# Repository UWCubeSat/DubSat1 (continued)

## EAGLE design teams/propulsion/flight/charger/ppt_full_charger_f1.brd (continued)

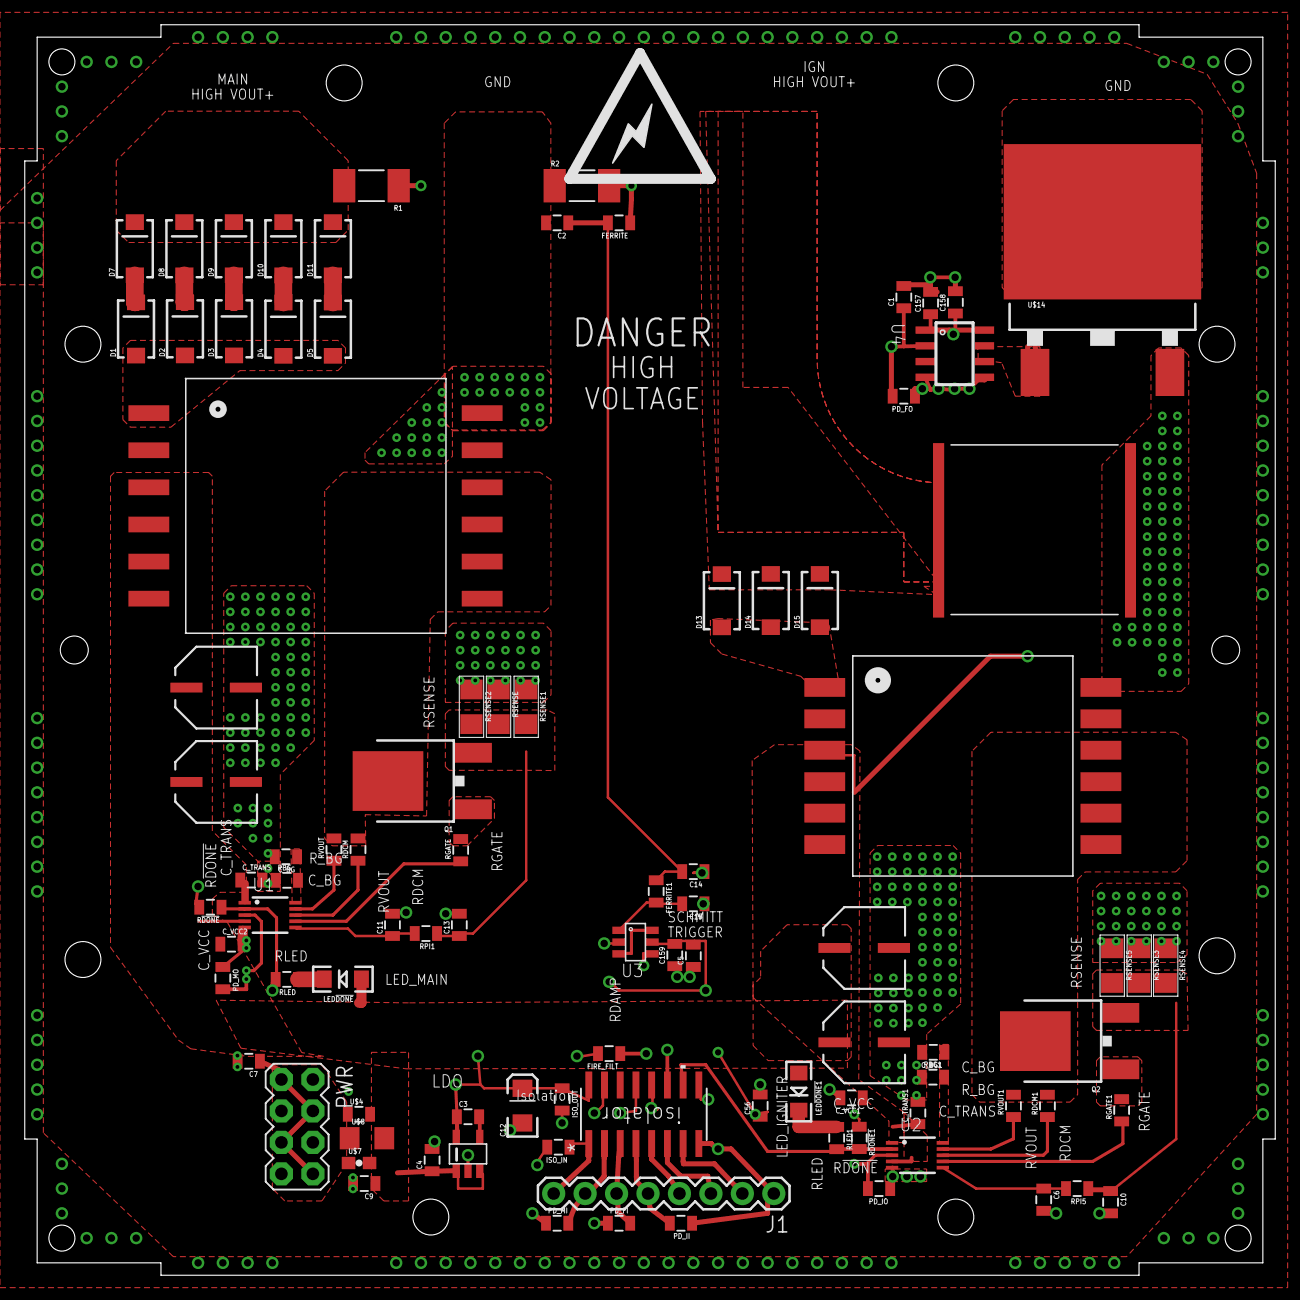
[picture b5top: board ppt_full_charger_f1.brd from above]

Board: 4 copper layers, 101.0 x 101.0 mm, 94 parts (0 on the bottom side), 51 nets.

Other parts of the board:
U$3: ICON_BOLT-L

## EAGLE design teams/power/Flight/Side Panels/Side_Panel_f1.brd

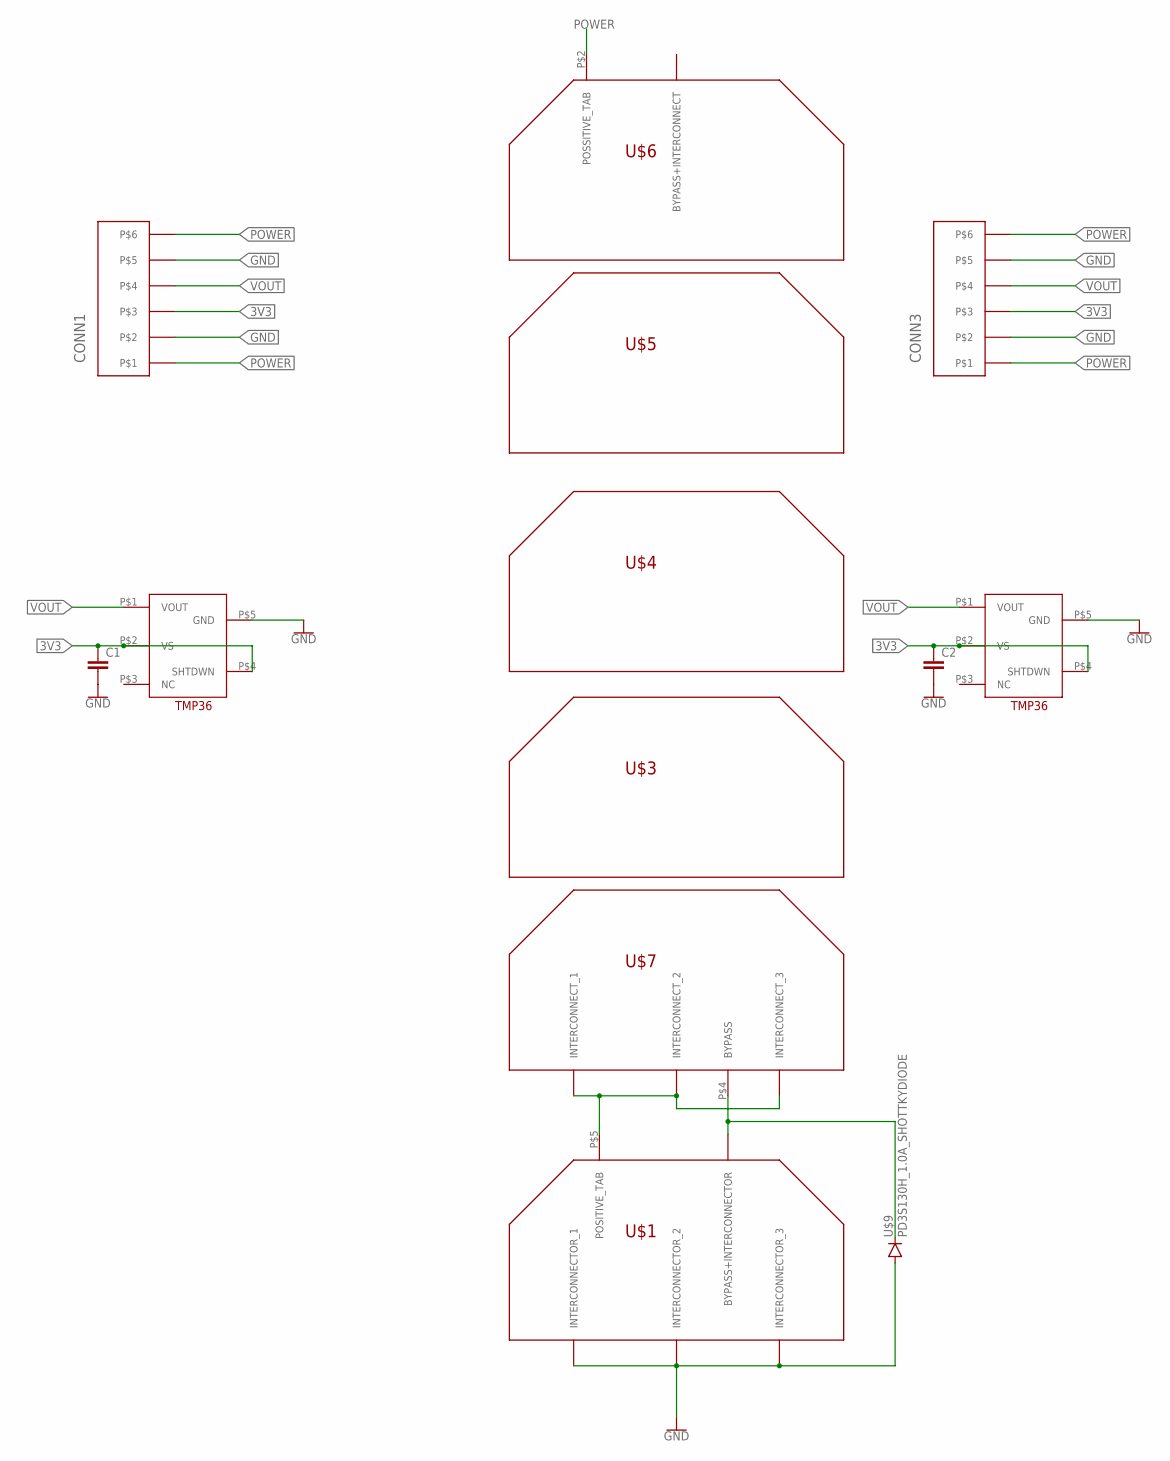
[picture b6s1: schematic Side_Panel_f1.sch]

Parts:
C1, C2: CAPACITOR0805; 0805
CONN1, CONN3: PICOLOCK_6PICOLOCK_6; PICOLOCK_6
U$1: SOLAR_CELL_STAND-ALONE
U$2, U$8: TMP36; SOT-23-5
U$3, U$4, U$5: SOALAR_CELL_OUTLINE; SOLAR_CELL_OUTLINE
U$6: SOLAR_CELL_TOP; SOLAR_CELL_TOP_SHORT-PAD
U$7: SOLAR_CELL_BOTTOM+BYPASS
U$9: PD3S130H_1.0A_SHOTTKYDIODE; POWERDI_323

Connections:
3V3: C1.1, C2.1, CONN1.P$3, CONN3.P$3, U$2.P$2 (VS), U$2.P$4 (SHTDWN), U$8.P$2 (VS), U$8.P$4 (SHTDWN)
GND: C1.2, C2.2, CONN1.P$2, CONN1.P$5, CONN3.P$2, CONN3.P$5, U$1.P$1 (INTERCONNECTOR_1), U$1.P$2 (INTERCONNECTOR_2), U$1.P$3 (INTERCONNECTOR_3), U$2.P$5 (GND), U$8.P$5 (GND), U$9.P$2 (A)
unnamed: U$1.P$4 (BYPASS+INTERCONNECTOR), U$7.P$4 (BYPASS), U$9.P$1 (C)
unnamed: U$1.P$5 (POSITIVE_TAB), U$7.P$1 (INTERCONNECT_1), U$7.P$2 (INTERCONNECT_2), U$7.P$3 (INTERCONNECT_3)
POWER: CONN1.P$1, CONN1.P$6, CONN3.P$1, CONN3.P$6, U$6.P$2 (POSSITIVE_TAB)
VOUT: CONN1.P$4, CONN3.P$4, U$2.P$1 (VOUT), U$8.P$1 (VOUT)

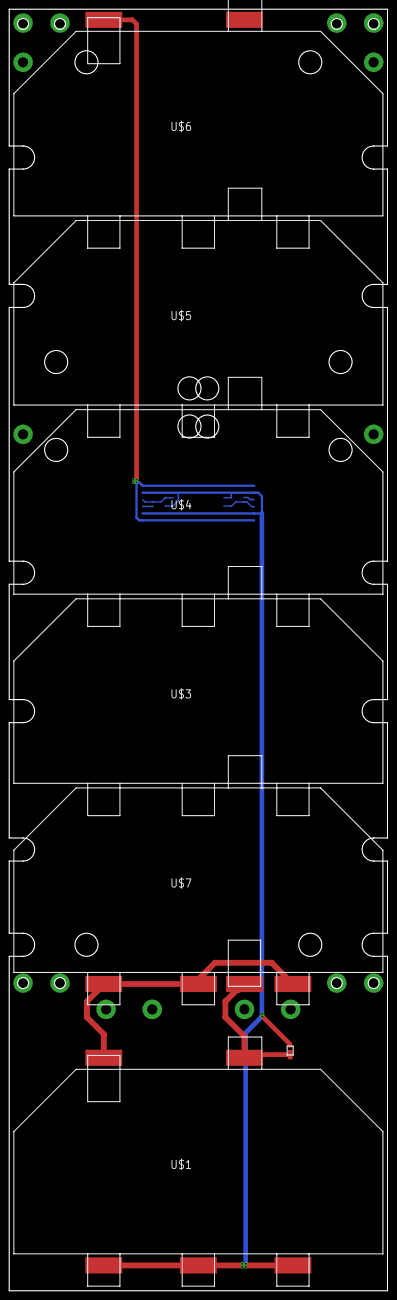
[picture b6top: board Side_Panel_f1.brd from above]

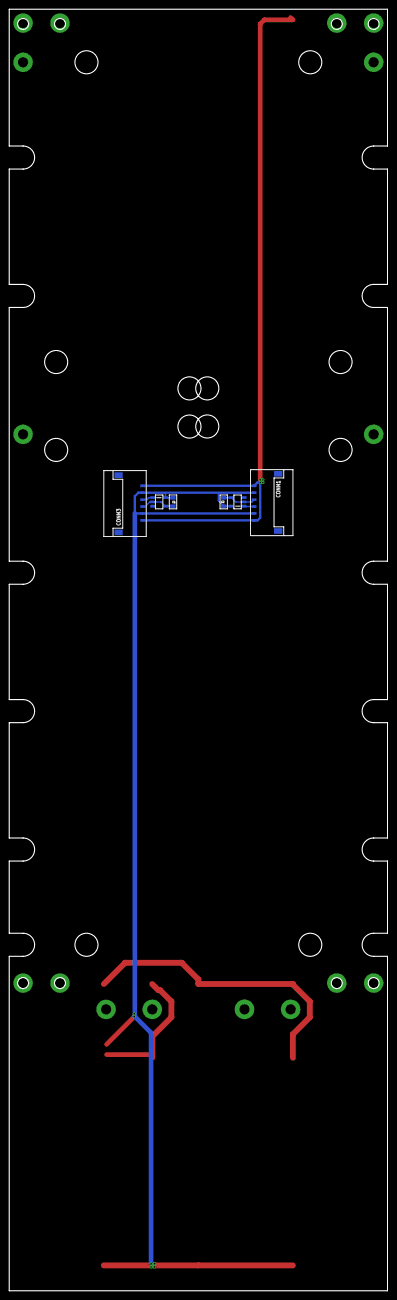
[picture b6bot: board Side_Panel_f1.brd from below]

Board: 2 copper layers, 82.0 x 277.8 mm, 13 parts (6 on the bottom side), 6 nets.

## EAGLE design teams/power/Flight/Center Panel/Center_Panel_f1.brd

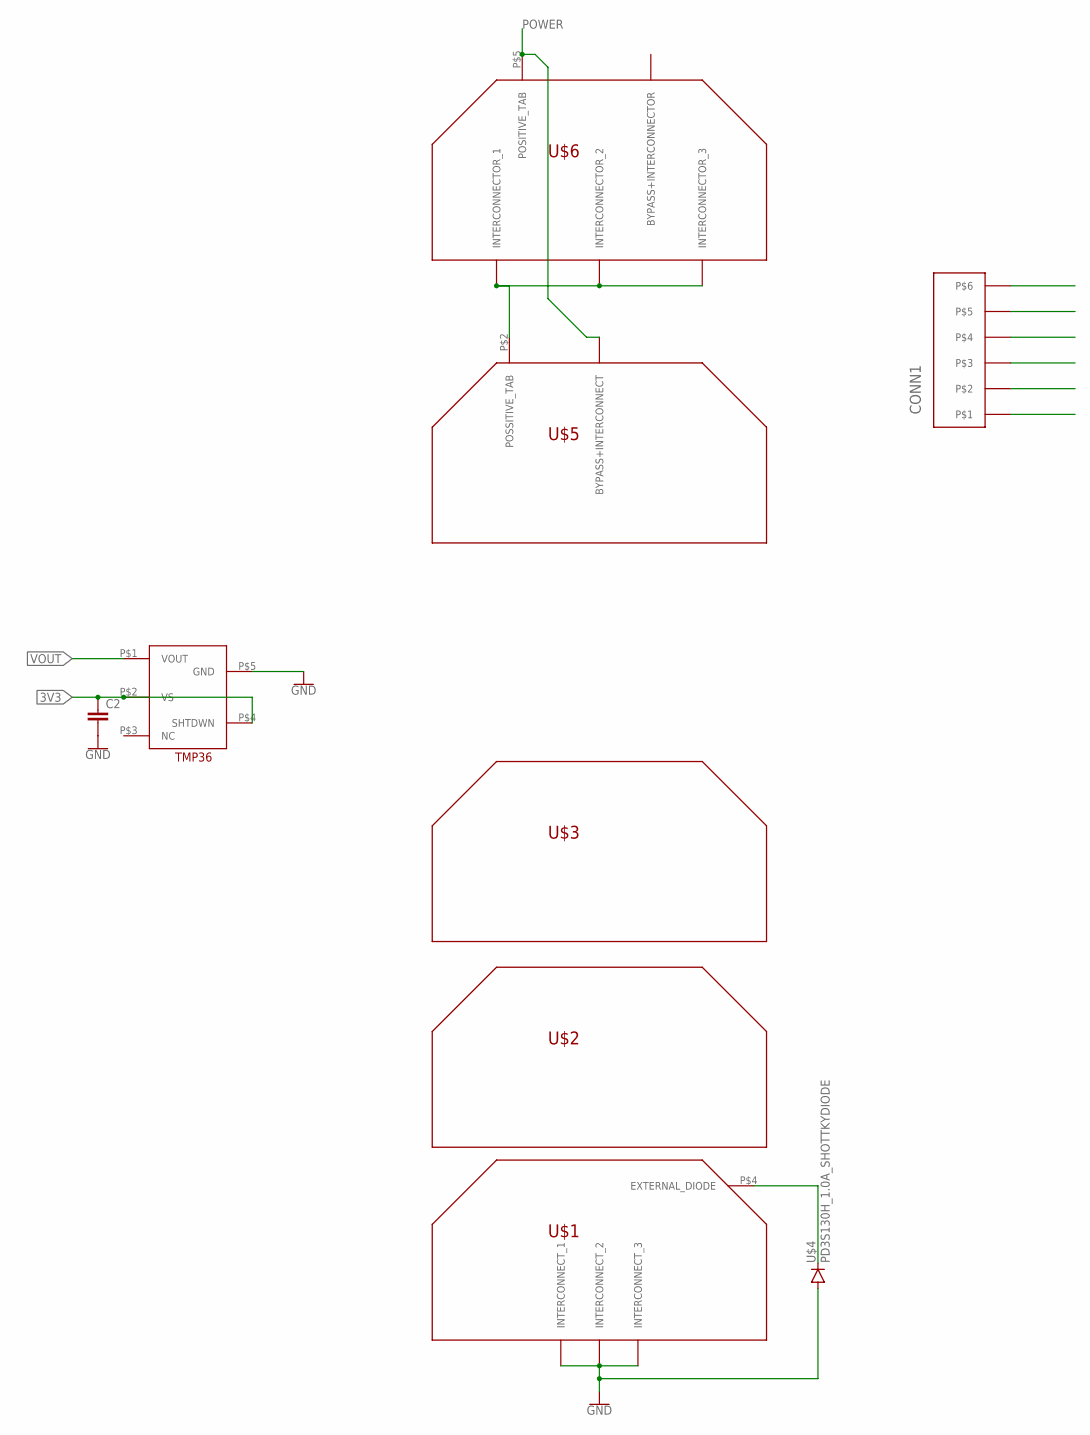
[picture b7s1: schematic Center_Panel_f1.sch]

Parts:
C2: CAPACITOR0805; 0805
CONN1: PICOLOCK_6
U$1: SOLAR_CELL_BOTTOM_W_DIODE; SOLAR_CELL_BOTTOM_SHORT-PADS
U$2, U$3: SOALAR_CELL_OUTLINE; SOLAR_CELL_OUTLINE
U$4: PD3S130H_1.0A_SHOTTKYDIODE; POWERDI_323
U$5: SOLAR_CELL_TOP; SOLAR_CELL_TOP_SHORT-PAD
U$6: SOLAR_CELL_STAND-ALONE
U$7: TMP36; SOT-23-5

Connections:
3V3: C2.1, CONN1.P$3, U$7.P$2 (VS), U$7.P$4 (SHTDWN)
GND: CONN1.P$2, CONN1.P$5, U$1.P$1 (INTERCONNECT_1), U$1.P$2 (INTERCONNECT_2), U$1.P$3 (INTERCONNECT_3), U$4.P$2 (A), U$7.P$5 (GND)
unnamed: U$5.P$2 (POSSITIVE_TAB), U$6.P$1 (INTERCONNECTOR_1), U$6.P$2 (INTERCONNECTOR_2), U$6.P$3 (INTERCONNECTOR_3)
unnamed: U$1.P$4 (EXTERNAL_DIODE), U$4.P$1 (C)
POWER: CONN1.P$1, CONN1.P$6, U$5.P$1 (BYPASS+INTERCONNECT), U$6.P$5 (POSITIVE_TAB)
VOUT: CONN1.P$4, U$7.P$1 (VOUT)

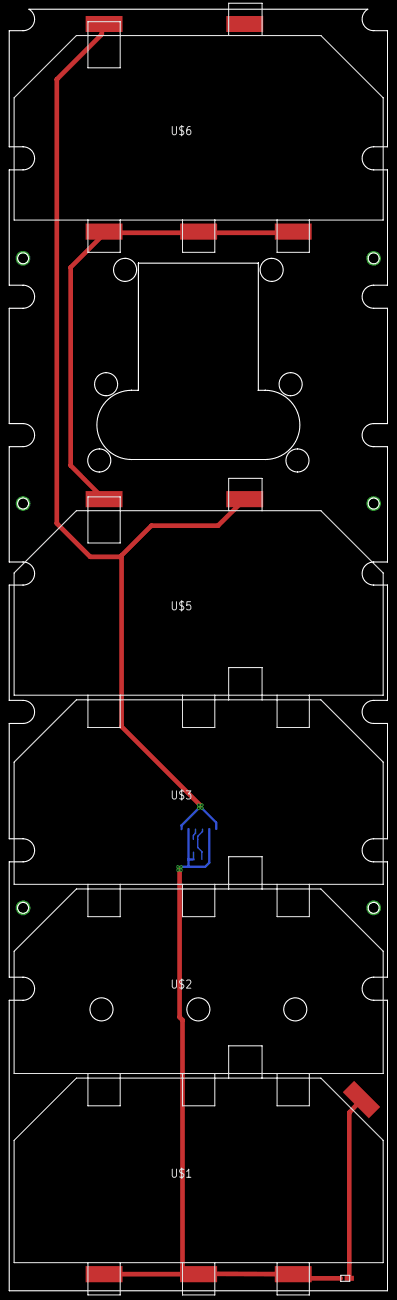
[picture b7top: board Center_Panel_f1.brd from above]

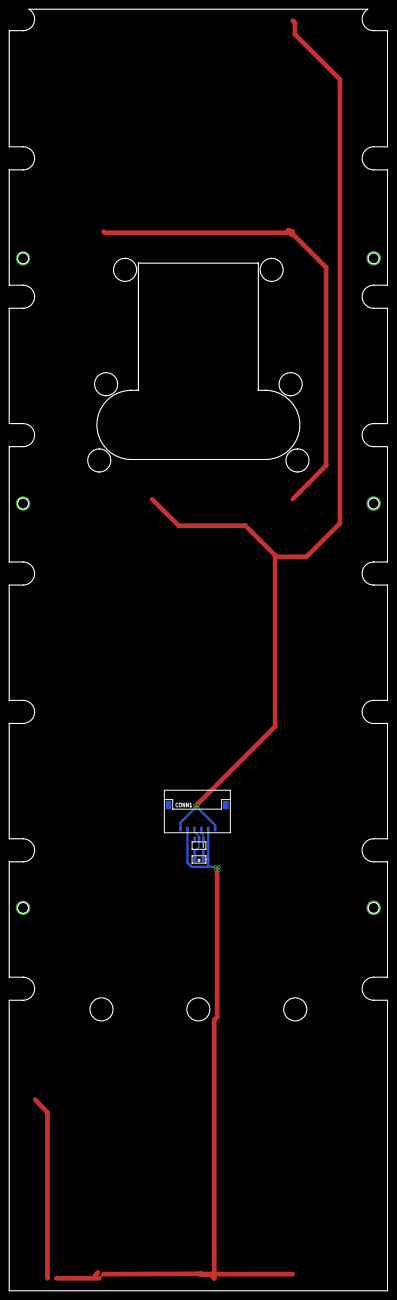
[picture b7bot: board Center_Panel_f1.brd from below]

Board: 2 copper layers, 82.0 x 277.8 mm, 9 parts (3 on the bottom side), 6 nets.

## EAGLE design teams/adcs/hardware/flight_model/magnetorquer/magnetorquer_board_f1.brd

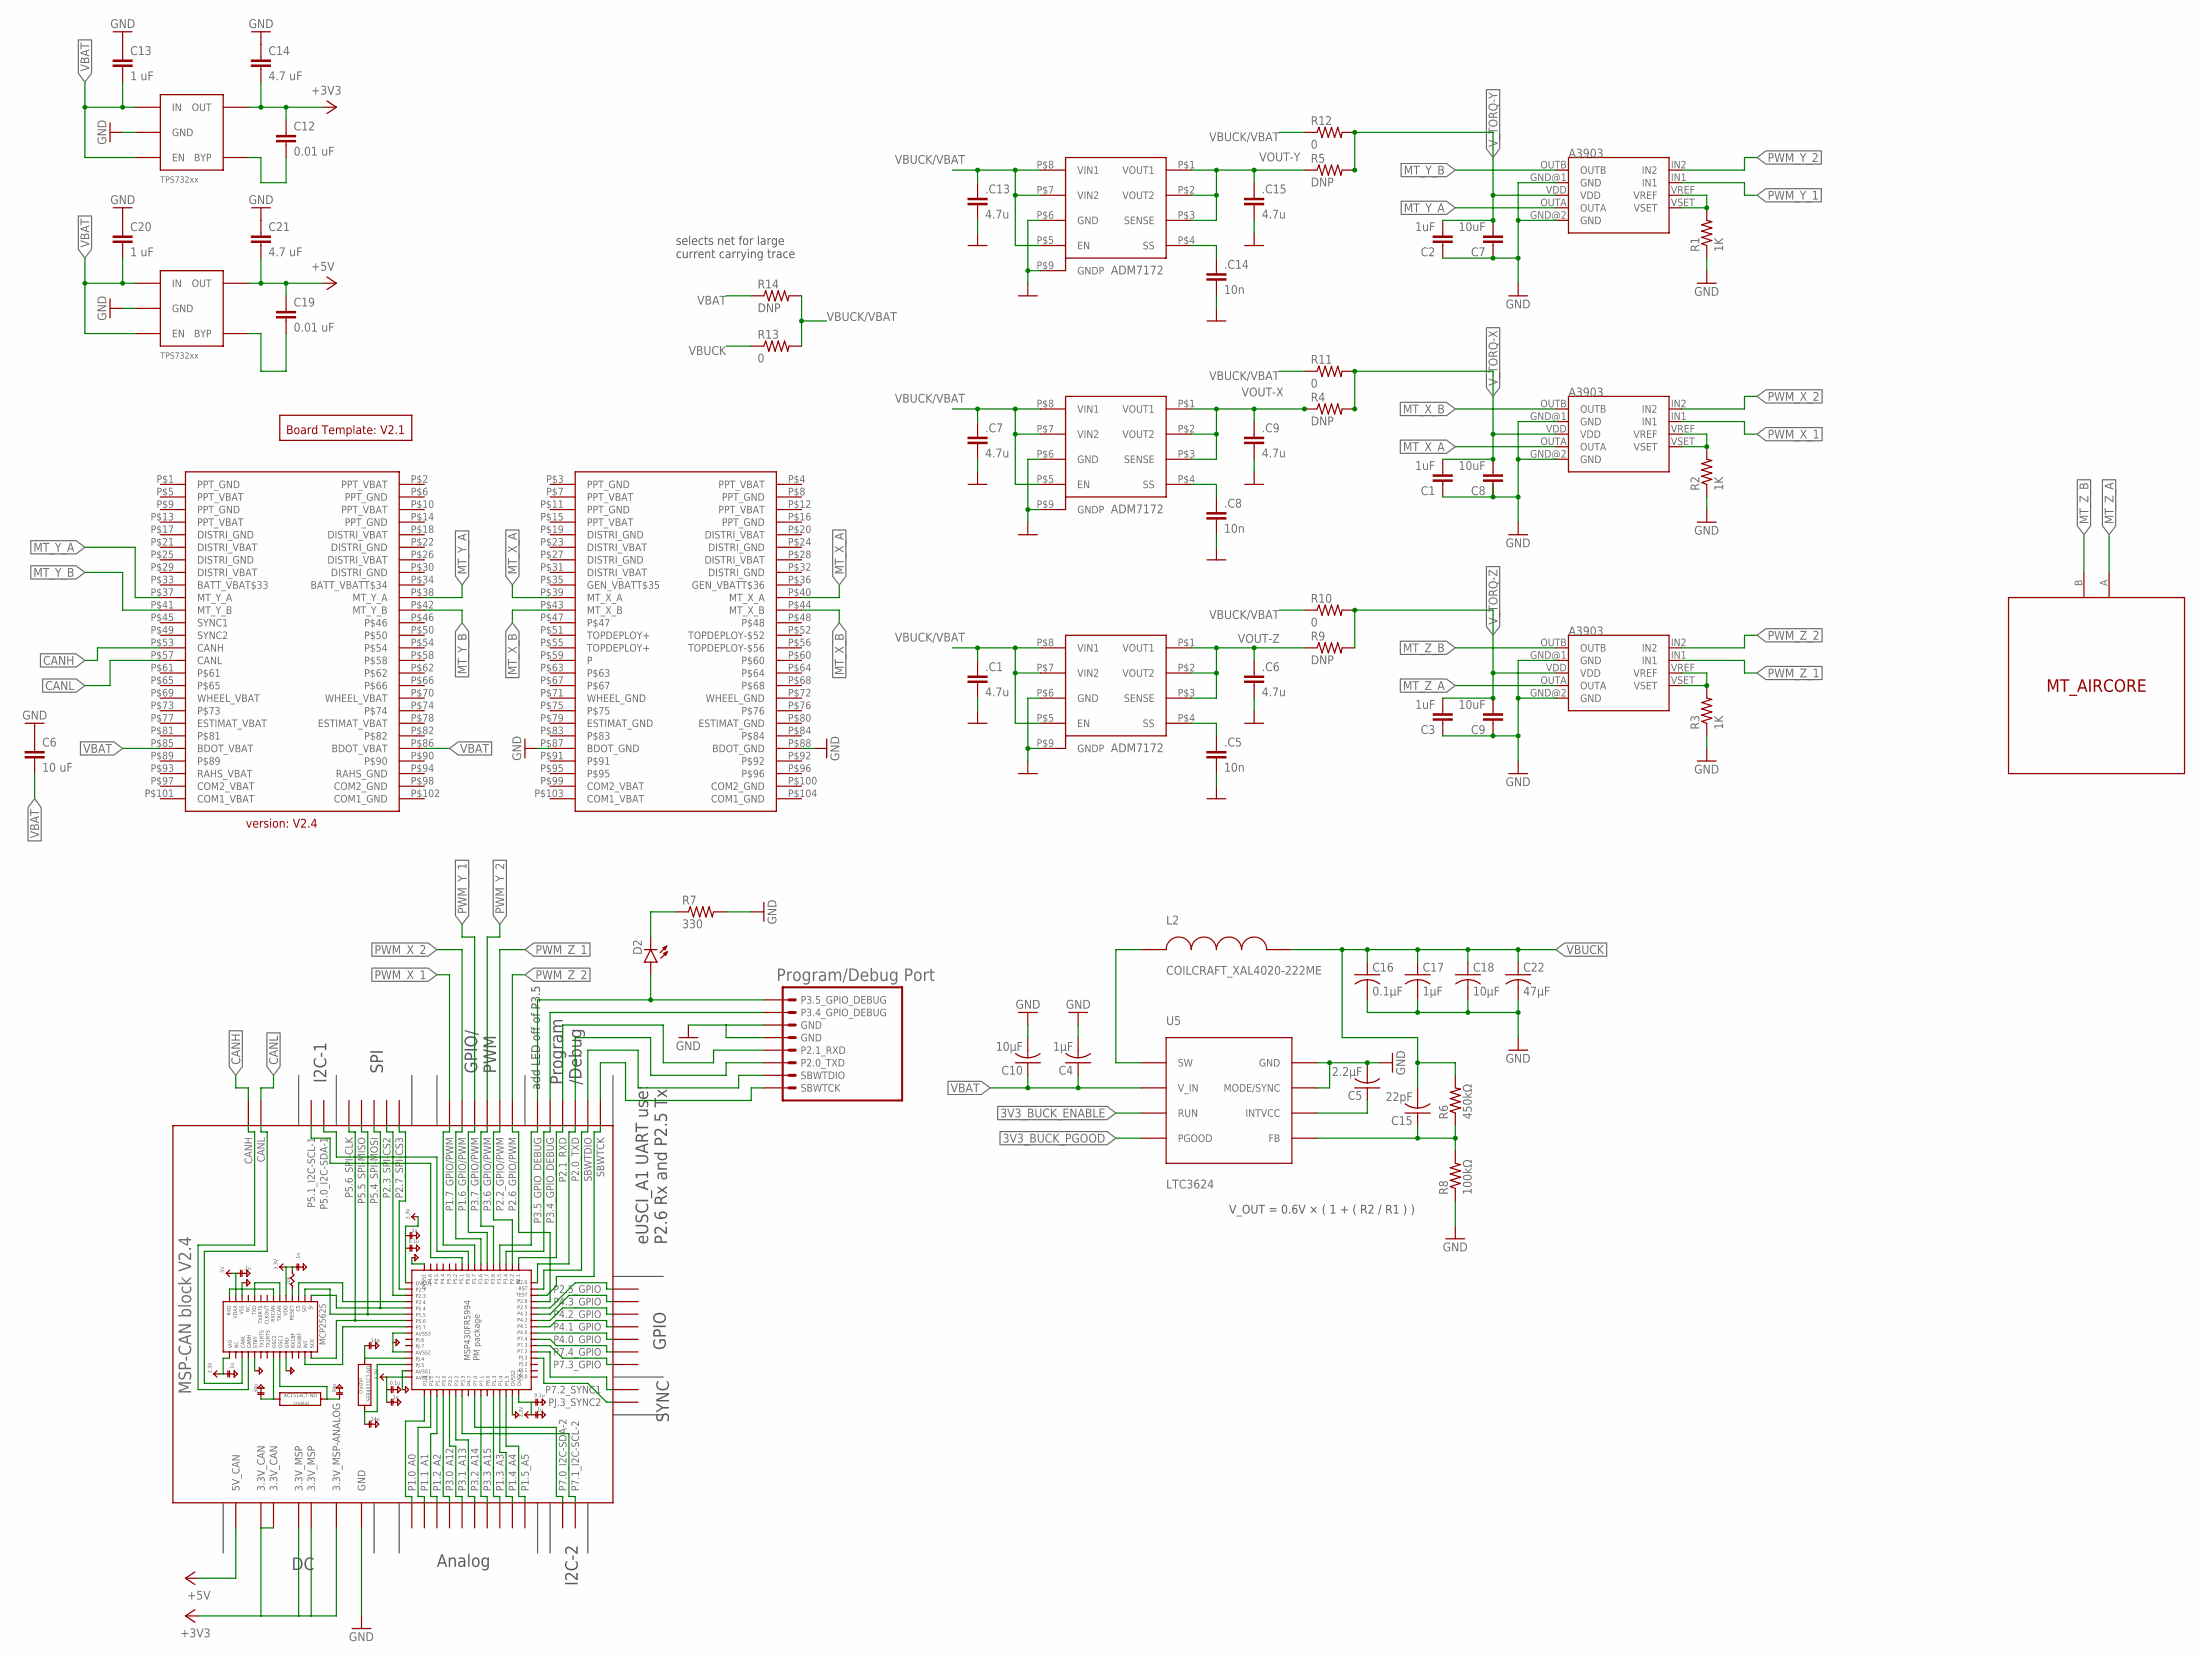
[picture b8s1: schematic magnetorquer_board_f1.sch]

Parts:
.C1, .C6, .C7, .C9, .C13, .C15: 4.7u; 1206
.C5, .C8, .C14: 10n; 0805
C1, C2, C3: 1uF; 0805
C4, C17: 1µF; C0805
C5: 2.2μF; C0805
C6: 10 uF; 0805
C7, C8, C9: 10uF; 0805
C10, C18: 10µF; C0805
C12, C19: 0.01 uF; 0805
C13, C20: 1 uF; 0805
C14, C21: 4.7 uF; 0805
C15: 22pF; C0805
C16: 0.1µF; C1206
C22: 47µF; C0805
D2: LED; LED-1206
L2: COILCRAFT_XAL4020-222ME; COILCRAFT_XAL4020
LDO_3V1, LDO_5V1: TPS732XX; SOT-23-5
R1, R2, R3: 1K; R0603
R4, R5, R9: DNP; 0805
R6: 450kΩ; R0805
R7: 330; 0805
R8: 100kΩ; R0805
R10, R11, R12: 0; 0805
R13: 0; R2010
R14: DNP; R2010
U1, U2, U3: A3903; DFN-8EE
U5: LTC3624
U$1: PC104_CONNECTOR
U$2: BOARD_TEMPLATE1; BOARD_TEMPLATE
U$3: MT_AIRCORE
U$4, U$5, U$9: ANALOG_LDO_ADM7172; 8-LFCSP
U$7: MSP-CAN_BLOCK
U$8: PROGRAM/DEBUG_PORT; 1X08_CONNECTOR

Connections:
3V3_BUCK_ENABLE: U5.RUN
3V3_BUCK_FB1: C15.1, R6.1, R8.2, U5.FB
3V3_BUCK_INTVCC1: C5.1, U5.INTVCC
3V3_BUCK_PGOOD: U5.PGOOD
3V3_BUCK_SW1: L2.P$1, U5.SW
+3V3: C12.1, C14.2, LDO_3V1.P$5 (OUT), U$7.3.3V@CAN1 (3.3V_CAN), U$7.3.3V@CAN2 (3.3V_CAN), U$7.3.3V@MSP1 (3.3V_MSP), U$7.3.3V@MSP2 (3.3V_MSP), U$7.3.3V_ANALOG@MSP2 (3.3V_MSP-ANALOG)
+5V: C19.1, C21.2, LDO_5V1.P$5 (OUT), U$7.5V (5V_CAN)
CANH: U$1.P$53 (CANH), U$7.CANH
CANL: U$1.P$57 (CANL), U$7.CANL
GND: .C1.2, .C5.2, .C6.2, .C7.2, .C8.2, .C9.2, .C13.2, .C14.2, .C15.2, C1.1, C2.1, C3.1, C4.2, C5.2, C6.1, C7.1, C8.1, C9.1, C10.2, C13.1, C14.1, C16.2, C17.2, C18.2, C20.1, C21.1, C22.2, LDO_3V1.P$2 (GND), LDO_5V1.P$2 (GND), R1.1, R2.1, R3.1, R7.2, R8.1, U1.GND@1 (GND), U1.GND@2 (GND), U2.GND@1 (GND), U2.GND@2 (GND), U3.GND@1 (GND), U3.GND@2 (GND), U5.GND@1 (GND), U5.GND@PAD (GND), U5.MODE/SYNC, U$1.P$87 (BDOT_GND), U$1.P$88 (BDOT_GND), U$4.P$6 (GND), U$4.P$9 (GNDP), U$5.P$6 (GND), U$5.P$9 (GNDP), U$7.GND@1 (GND), U$7.GND@2 (GND), U$7.GND@3 (GND), U$7.GND@4 (GND), U$7.GND@5 (GND), U$7.GND@7 (GND), U$7.GND@8 (GND), U$7.GND@9 (GND), U$7.GND@10 (GND), U$7.GND@11 (GND), U$7.GND@12 (GND), U$7.GND@13 (GND), U$7.GND@14 (GND), U$7.GND@15 (GND), U$7.GND@16 (GND), U$7.GND@17 (GND), U$7.GND@26 (GND), U$8.5 (GND), U$8.6 (GND), U$9.P$6 (GND), U$9.P$9 (GNDP)
MT_X_A: U2.OUTA, U$1.P$39 (MT_X_A), U$1.P$40 (MT_X_A)
MT_X_B: U2.OUTB, U$1.P$43 (MT_X_B), U$1.P$44 (MT_X_B)
MT_Y_A: U1.OUTA, U$1.P$37 (MT_Y_A), U$1.P$38 (MT_Y_A)
MT_Y_B: U1.OUTB, U$1.P$41 (MT_Y_B), U$1.P$42 (MT_Y_B)
MT_Z_A: U3.OUTA, U$3.A; also elsewhere on the board
MT_Z_B: U3.OUTB, U$3.B; also elsewhere on the board
unnamed: R1.2, U1.VREF, U1.VSET
unnamed: R2.2, U2.VREF, U2.VSET
unnamed: D2.C, R7.1
unnamed: C12.2, LDO_3V1.P$4 (BYP)
unnamed: R3.2, U3.VREF, U3.VSET
unnamed: C19.2, LDO_5V1.P$4 (BYP)
unnamed: .C5.1, U$4.P$4 (SS)
unnamed: .C8.1, U$5.P$4 (SS)
unnamed: .C14.1, U$9.P$4 (SS)
unnamed: U$7.SBWTCK, U$8.SBWTCK
unnamed: U$7.SBWTDIO, U$8.2 (SBWTDIO)
unnamed: U$7.P2.0_TXD, U$8.3 (P2.0_TXD)
unnamed: U$7.P2.1_RXD, U$8.4 (P2.1_RXD)
unnamed: U$7.P3.4_GPIO_DEBUG, U$8.7 (P3.4_GPIO_DEBUG)
unnamed: D2.A, U$7.P3.5_GPIO_DEBUG, U$8.8 (P3.5_GPIO_DEBUG)
PWM_X_1: U2.IN1, U$7.P1.7_GPIO/PWM
PWM_X_2: U2.IN2, U$7.P1.6_GPIO/PWM
PWM_Y_1: U1.IN1, U$7.P3.7_GPIO/PWM
PWM_Y_2: U1.IN2, U$7.P3.6_GPIO/PWM
PWM_Z_1: U3.IN1, U$7.P2.2_GPIO/PWM
PWM_Z_2: U3.IN2, U$7.P2.6_GPIO/PWM
VBAT: C4.1, C6.2, C10.1, C13.2, C20.2, LDO_3V1.P$1 (IN), LDO_3V1.P$3 (EN), LDO_5V1.P$1 (IN), LDO_5V1.P$3 (EN), R14.1, U5.V_IN, U$1.P$85 (BDOT_VBAT), U$1.P$86 (BDOT_VBAT)
VBUCK: C15.2, C16.1, C17.1, C18.1, C22.1, L2.P$2, R6.2, R13.1
VBUCK/VBAT: .C1.1, .C7.1, .C13.1, R10.1, R11.1, R12.1, R13.2, R14.2, U$4.P$5 (EN), U$4.P$7 (VIN2), U$4.P$8 (VIN1), U$5.P$5 (EN), U$5.P$7 (VIN2), U$5.P$8 (VIN1), U$9.P$5 (EN), U$9.P$7 (VIN2), U$9.P$8 (VIN1)
VOUT-X: .C9.1, R4.1, U$5.P$1 (VOUT1), U$5.P$2 (VOUT2), U$5.P$3 (SENSE)
VOUT-Y: .C15.1, R5.1, U$9.P$1 (VOUT1), U$9.P$2 (VOUT2), U$9.P$3 (SENSE)
VOUT-Z: .C6.1, R9.1, U$4.P$1 (VOUT1), U$4.P$2 (VOUT2), U$4.P$3 (SENSE)
V_TORQ-X: C1.2, C8.2, R4.2, R11.2, U2.VDD
V_TORQ-Y: C2.2, C7.2, R5.2, R12.2, U1.VDD
V_TORQ-Z: C3.2, C9.2, R9.2, R10.2, U3.VDD

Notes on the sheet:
V_OUT = 0.6V × ( 1 + ( R2 / R1 ) )
selects net for large current carrying trace

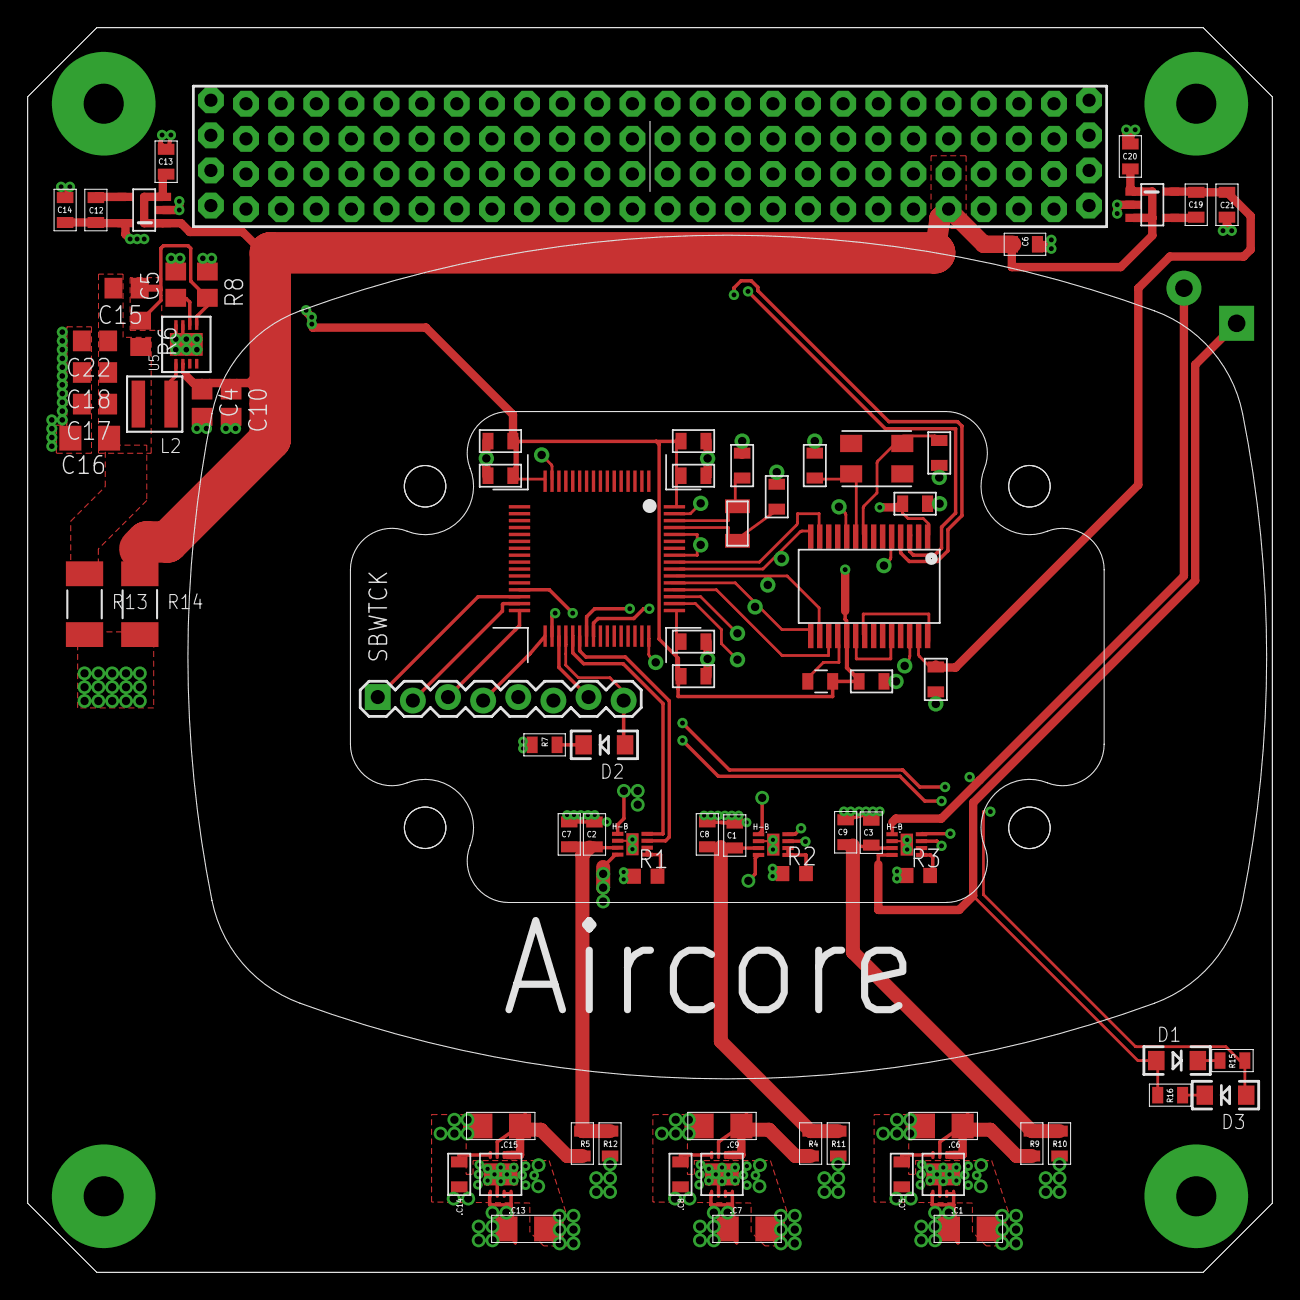
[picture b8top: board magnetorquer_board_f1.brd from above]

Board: 4 copper layers, 90.0 x 90.0 mm, 64 parts (0 on the bottom side), 46 nets.

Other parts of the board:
D1, D3: LED-1206
R15, R16: 330; 0805

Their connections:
MT_Z_A: D1.A, R16.1; also elsewhere on the board
MT_Z_B: D3.A, R15.2; also elsewhere on the board
unnamed: D3.C, R16.2
unnamed: D1.C, R15.1

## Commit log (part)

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2018-05-26 ADCS/Estim: Use SWISSCUBE TLE to match simulink
2018-05-26 ADCS/Sensor proc.: Send unfiltered mag input as output temporarily
2018-05-26 Add IMU glitch filter
2018-05-26 Add sun sensor glitch filter
2018-05-27 made changes on batt from SOC to acc charge
2018-05-27 Add reset timestamp to sendData script
2018-05-27 Various stuff
2018-05-27 Cleaning up Europa ...
2018-05-27 Added more features to magnetometer filter including signed comparisons
2018-05-28 0x08 != 0x80
2018-05-29 Added glitter count to help debug glitches for the magnetometer
2018-05-29 added bdot telemtry
2018-05-30 ADCS/Sensor proc.: Update rollcall packets
2018-05-31 ADCS/Sensor proc.: Tidy up and add documentation
2018-05-31 made changes to test
2018-06-02 ADCS/Estim: Add TLE id to rollcall
2018-06-03 ADCS/Estim: wait for CAN buffer to empty
2018-06-03 Fix sensor proc units in dbc
2018-06-03 Add missing units to estim and FSW (for formatting)
2018-06-04 added u as unit for unit vectors
2018-06-05 fix for overflow issue
2018-06-07 Got rid of all but the least magic of numbers in can.c
2018-06-08 added nap functionality to bdot
2018-06-10 reorganize bdot code to add NAP feature, Magnetometer Testing mode, along with cosmos commands for nap and mag testing
2018-06-10 fixed id of cmd_gen_rst
2018-06-11 quick fix to gen backpwr
2018-06-11 changed ids to match spreadsheet
2018-06-11 fixed backpower on gen, minor changes to dist
2018-06-12 made nap bug better/disappear
2018-06-12 added a helper function to bsp for Paul's fix
2018-06-13 added nathans units
2018-06-13 changed the float compression to multiplication and division, initialized aggVecs in gen, added other temperature ags in dist
2018-06-14 fixed merged conflict in cproject - bdot
2018-06-14 changed units to match nathans specfications
2018-06-15 added mtq pms
2018-06-15 added helper bash script for generating cosmos files and canwrap files
2018-06-15 added correct signage for eps rc
2018-06-15 added sequential xyz dipoles for SPAM
2018-06-16 emptied packet 1 created health packet1
2018-06-16 work in progress
2018-06-16 ADCS/FSW: Update omega rollcall
    For issue #195
2018-06-16 Update canwrap
2018-06-17 bdot main for testing calibration
2018-06-19 changed sign of temperature and unit
2018-06-19 fixed a bug where bdot's reported magnetometer averages reported over CAN were incorrect
2018-06-20 fixed rollcall resetting on MTQ
2018-06-20 changed min and max of pms
2018-06-20 added PMS_PHASE to mtq ack packet
2018-06-21 fix spam bug + cleanup code
2018-06-22 added added spam control
2018-06-22 added mode operation gcmd in CAN
2018-06-22 fixed size of spam on
2018-06-23 ADCS/Sensor proc: Fix sun sensor unit conversion to int
2018-06-25 removed line breaks
2018-06-25 add mtq pwm time
2018-06-26 got PPT up to speed with agglib and CAN, cleaned up code; UNTESTED
2018-06-27 ADCS/FSW: Increase stack size
    It's free real estate
2018-06-28 added missing data to MTQ rollcall
2018-06-29 bringing up to date
2018-06-29 began adding monitoring stuff
2018-06-29 fixed the persistence bug with the autosequencer on dist
2018-06-30 ADCS/Sensor proc.: Fix mag rollcall
    Fixes #180
2018-07-01 began to add changes for burns
2018-07-02 added result of fire to PPT, removed dataArray files
2018-07-02 chyanged some small things
2018-07-02 flipped overflow
2018-07-04 chugging along
2018-07-05 fixed ppt main done timing
2018-07-05 added PPT fire and fault counts, last fire result; made all of MTQ's rc_2 signed ints
2018-07-05 added PPT last fire result and fault count to rollcall
2018-07-06 added send flag to autosequencer add packet 1
2018-07-06 handled autosequencer CAN packets on dist
2018-07-09 changed batt's 'MET of last charge' to 'time since last charge'
2018-07-09 cahnges to dbc
2018-07-10 pushing unsaved changes to batt file; see last commit for details
2018-07-10 changed voltage to current in dbc
2018-07-10 updated monitor to monitor all RC
2018-07-11 added variance for bdot and mtq values to dbc
2018-07-12 working version of bdot before changing for independent mag self test
2018-07-12 fixed a bug where dist would report the incorrect power state for domains; will help fix #218
2018-07-12 fixed a bug where gen would not send panel enabled and charging flags properly
2018-07-13 fixed more issues that were lost in the dbc merge
2018-07-13 added back bdot variance
2018-07-13 changed names of autosequencer response packets
2018-07-16 changed dbc ready to run id replace
2018-07-16 updated dbc and canwrap
2018-07-16 reverted rollcall ID
2018-07-17 latest
2018-07-18 no message
2018-07-18 added parameters for specific subsystems in reset_minmax; added a packet for dist autoshutoff
2018-07-19 tested all bdot cmds, fixed bugs
2018-07-19 added counts for bytes read/written to the i2c lib; removed logic that could lead to inflated i2c error counts
2018-07-21 Fix IMU endianness
2018-07-23 minor fix to i2c waits
2018-07-24 fixed a bug in dist's autoshutoff where a pd couldn't be turned back on after a shutoff of any kind
2018-07-26 removed autostart on dist for Con-Ops testing
2018-07-27 added a command to set the automation state for battery balancing
2018-07-27 added values for sysrstiv
2018-07-28 added i2c results to sp rollcall 17
2018-07-31 changes to the way the PPT fires and the reporting logic
2018-07-31 added reporting for battery heater and balancer automation states
2018-08-01 added a command to enable/disable the autosequencer
2018-08-01 updates to ppt commands and rollcall
2018-08-02 cleared reset counts on reset mission command
2018-08-02 removed setting bdot to auto-determine magnetometer
2018-08-03 added signals for bdot gain factors
2018-08-03 added units to bdot gain for conversions
2018-08-06 added magnetorquer phase to magnetometer readings
2018-08-15 moved 7 packets into WOD and 1 out
2018-08-24 moved COM2 and RAHS timed shutoffs to timer lib (independent of the autosequencer) add pd states for autoshutoff
2018-09-18 created dedicated wod packets, reclassified old wod packets
2018-09-21 missed some unsaved changes
2018-10-28 implemented the double clearing logic on batt for battV_avg
2018-10-29 Made a script to re-do CAN IDs
2018-10-30 regen of canwrap after ground class bit changes
2018-11-07 changed the battery undervoltage threshold from 5.2V to 6.0V
2018-11-30 ADCS/Sensor proc.: Simplify sensor interfaces
2018-12-05 Remove non-GPS code from sensor proc
2018-12-19 updated AMSAT pins on PC104 connector
2019-01-31 code to generate version 3 of the CAN Model
2019-02-03 changed the ina averageing window from 68ms to 1ms
2019-02-06 changed SADC bits properly this time
2019-02-06 re-added the config with the default sampling
2019-02-17 added packets to the dbc for camera data and COM1 commands
2019-02-21 bad merge
2019-02-23 changed senders in the dbc to allow for better COSMOS cmd generation
2019-02-23 new *.dbf generation
2019-02-25 last fixes for DBC revert
2019-03-08 fixed a bug in batt's time since last full charge
2019-03-09 removed unused packets from the dbc
2019-03-10 updated bdot_mag_control value table
2019-03-22 fixed a bug where the reason for shutoff on power domains could be reported incorrectly
2019-03-22 added a packet to the dbc for bdot mag variance
2019-03-30 fixed DLCs in the dbc
2019-03-30 added signals for mag variance from sensorproc to the dbc
2019-04-20 duplicated WOD signals on batt and dist
2019-04-21 added simple test harness for barebones magnetometer reading
2019-04-30 Added conversion from LonLat packets to DM packets
2019-05-09 fixed a bug where the i2c library wouldn't initialize properly
2019-05-14 Multiplication sign @Nathan
2019-05-17 Added a test file for the GPS and a main file for the Phat1 board. Also modified the UART.c code to havve registers appropriate for the launchpad.
2019-05-17 New main file that works. I2C works.
2019-05-21 found bug in conversion of position to lonlat
2019-05-23 working version of gps without sending uart data
2019-05-28 changed uart back to use UCA1
2019-05-29 added magnetometer functionality
2019-05-30 general updates
2019-05-30 added COMS transmission stuff in the format. currently just running test code
2019-07-16 test code for GPS
2019-12-19 Bump rack from 2.0.3 to 2.0.8 in /grnd/experiments/ArdMOS/cosmos
    Bumps [rack](https://github.com/rack/rack) from 2.0.3 to 2.0.8.
    - [Release notes](https://github.com/rack/rack/releases)
    - [Changelog](https://github.com/rack/rack/blob/master/CHANGELOG.md)
    - [Commits](https://github.com/rack/rack/compare/2.0.3...2.0.8)
2020-02-25 Bump nokogiri from 1.8.1 to 1.10.8 in /grnd/COSMOS/Demo
    Bumps [nokogiri](https://github.com/sparklemotion/nokogiri) from 1.8.1 to 1.10.8.
    - [Release notes](https://github.com/sparklemotion/nokogiri/releases)
    - [Changelog](https://github.com/sparklemotion/nokogiri/blob/master/CHANGELOG.md)
    - [Commits](https://github.com/sparklemotion/nokogiri/compare/v1.8.1...v1.10.8)
2021-05-19 Bump nokogiri from 1.8.1 to 1.11.4 in /grnd/COSMOS/Demo
    Bumps [nokogiri](https://github.com/sparklemotion/nokogiri) from 1.8.1 to 1.11.4.
    - [Release notes](https://github.com/sparklemotion/nokogiri/releases)
    - [Changelog](https://github.com/sparklemotion/nokogiri/blob/main/CHANGELOG.md)
    - [Commits](https://github.com/sparklemotion/nokogiri/compare/v1.8.1...v1.11.4)
2021-09-27 Bump nokogiri from 1.8.1 to 1.12.5 in /grnd/experiments/ArdMOS/cosmos
    Bumps [nokogiri](https://github.com/sparklemotion/nokogiri) from 1.8.1 to 1.12.5.
    - [Release notes](https://github.com/sparklemotion/nokogiri/releases)
    - [Changelog](https://github.com/sparklemotion/nokogiri/blob/main/CHANGELOG.md)
    - [Commits](https://github.com/sparklemotion/nokogiri/compare/v1.8.1...v1.12.5)
    ---
    updated-dependencies:
2022-02-26 Bump nokogiri from 1.8.1 to 1.13.3 in /grnd/COSMOS/Demo
    Bumps [nokogiri](https://github.com/sparklemotion/nokogiri) from 1.8.1 to 1.13.3.
    - [Release notes](https://github.com/sparklemotion/nokogiri/releases)
    - [Changelog](https://github.com/sparklemotion/nokogiri/blob/main/CHANGELOG.md)
    - [Commits](https://github.com/sparklemotion/nokogiri/compare/v1.8.1...v1.13.3)
    ---
    updated-dependencies:
2022-04-11 Bump nokogiri from 1.8.1 to 1.13.4 in /grnd/experiments/ArdMOS/cosmos
    Bumps [nokogiri](https://github.com/sparklemotion/nokogiri) from 1.8.1 to 1.13.4.
    - [Release notes](https://github.com/sparklemotion/nokogiri/releases)
    - [Changelog](https://github.com/sparklemotion/nokogiri/blob/v1.13.4/CHANGELOG.md)
    - [Commits](https://github.com/sparklemotion/nokogiri/compare/v1.8.1...v1.13.4)
    ---
    updated-dependencies:
